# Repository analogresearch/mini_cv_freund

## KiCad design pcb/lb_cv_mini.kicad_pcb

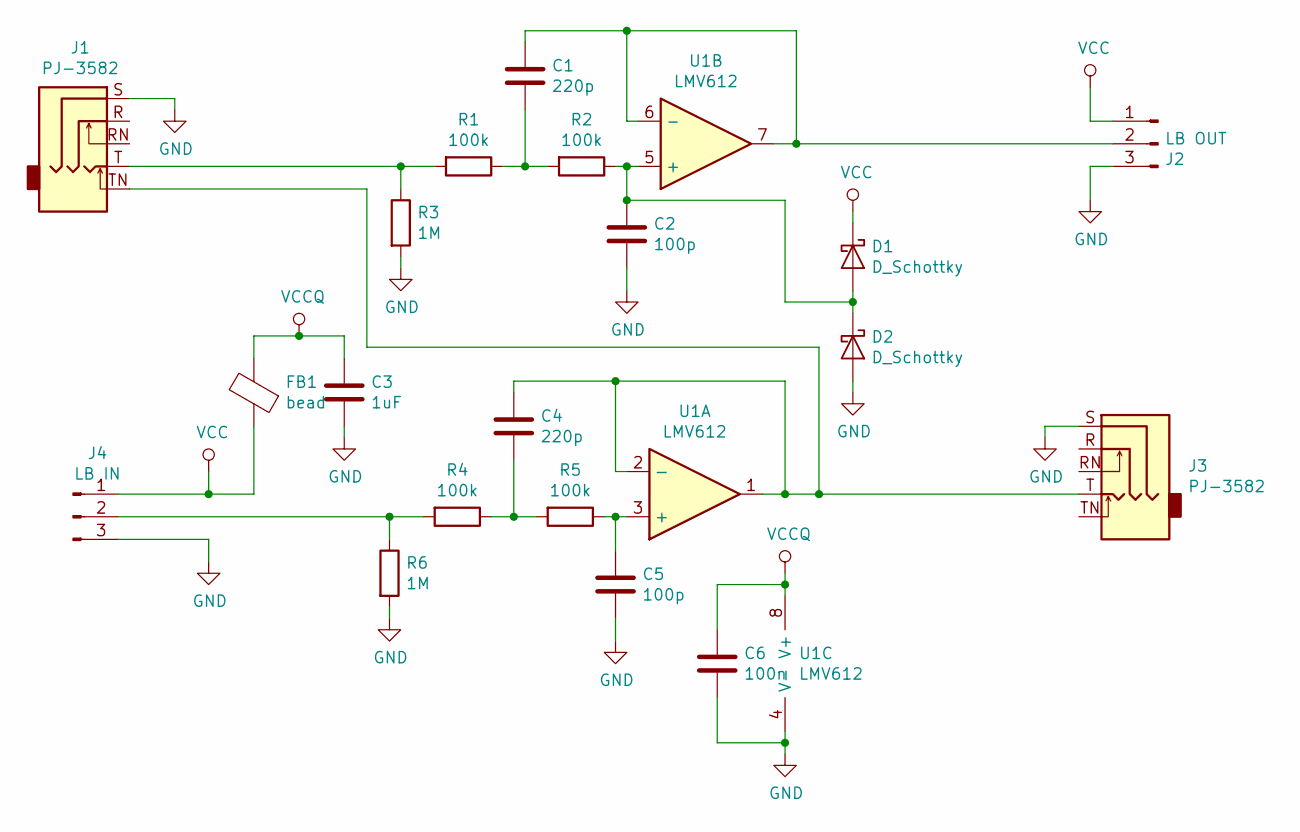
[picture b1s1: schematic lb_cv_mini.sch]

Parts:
C1, C4: 220p; C_0805_2012Metric; LCSC CL21B221KBANNNC
C2, C5: 100p; C_0805_2012Metric; LCSC CL21C101JBANNNC
C3: 1uF; C_0805_2012Metric; LCSC CL21B105KBFNNNE
C6: 100n; C_0805_2012Metric; LCSC CC0805KRX7R9BB104
D1, D2: D_Schottky; D_SOD-123; LCSC B5819W
FB1: bead; L_0805_2012Metric; LCSC GZ2012D101TF
J1, J3: PJ-3582
J2: LB OUT; bitsnaps_output
J4: LB IN; bitsnaps_input
R1, R2, R4, R5: 100k; R_0805_2012Metric; LCSC 0805W8F1003T5E
R3, R6: 1M; R_0805_2012Metric; LCSC 0805W8F1004T5E
U1: LMV612; VSSOP-8_3.0x3.0mm_P0.65mm; LCSC LMV612MMX/NOPB

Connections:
GND: C2.1, C3.2, C5.1, C6.2, D2.2 (A), J1.S, J2.3, J3.S, J4.3, R3.2, R6.2, U1.4 (V-)
unnamed: C1.1, J2.2, U1.6 (-), U1.7
unnamed: C1.2, R1.1, R2.2
unnamed: C2.2, D1.2 (A), D2.1 (K), R2.1, U1.5 (+)
unnamed: C4.1, J1.TN, J3.T, U1.1, U1.2 (-)
unnamed: C4.2, R4.1, R5.2
unnamed: C5.2, R5.1, U1.3 (+)
unnamed: J1.T, R1.2, R3.1
unnamed: J4.2, R4.2, R6.1
VCC: D1.1 (K), FB1.1, J2.1, J4.1
VCCQ: C3.1, C6.1, FB1.2, U1.8 (V+)

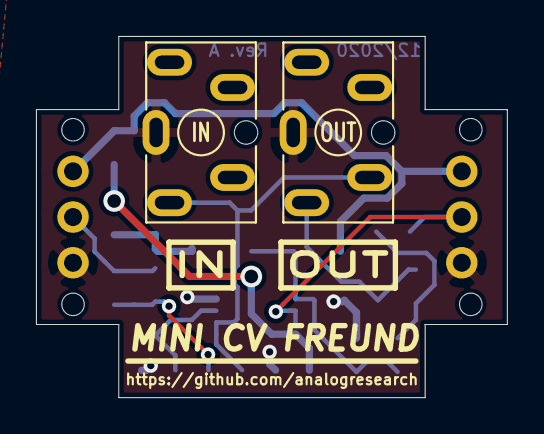
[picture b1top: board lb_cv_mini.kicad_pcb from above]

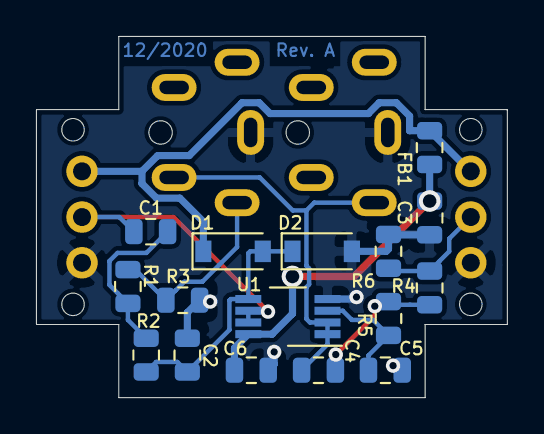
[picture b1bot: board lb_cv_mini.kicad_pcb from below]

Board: 2 copper layers, 26.2 x 20.1 mm, 20 parts (16 on the bottom side), 11 nets.

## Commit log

2020-12-02 inital commit
2020-12-02 added pcb layout
